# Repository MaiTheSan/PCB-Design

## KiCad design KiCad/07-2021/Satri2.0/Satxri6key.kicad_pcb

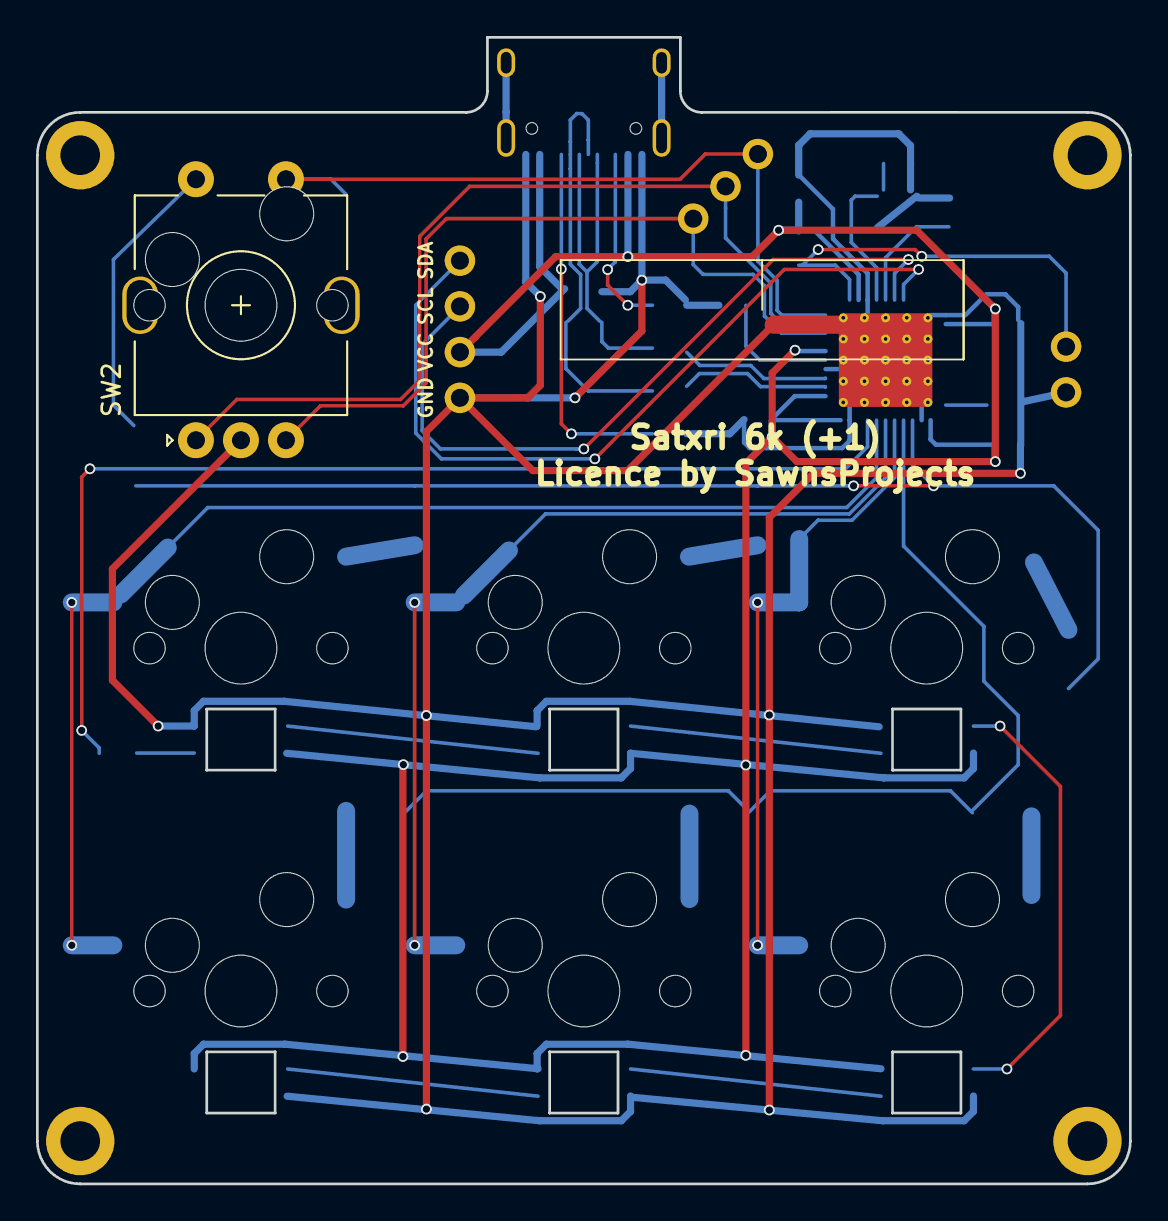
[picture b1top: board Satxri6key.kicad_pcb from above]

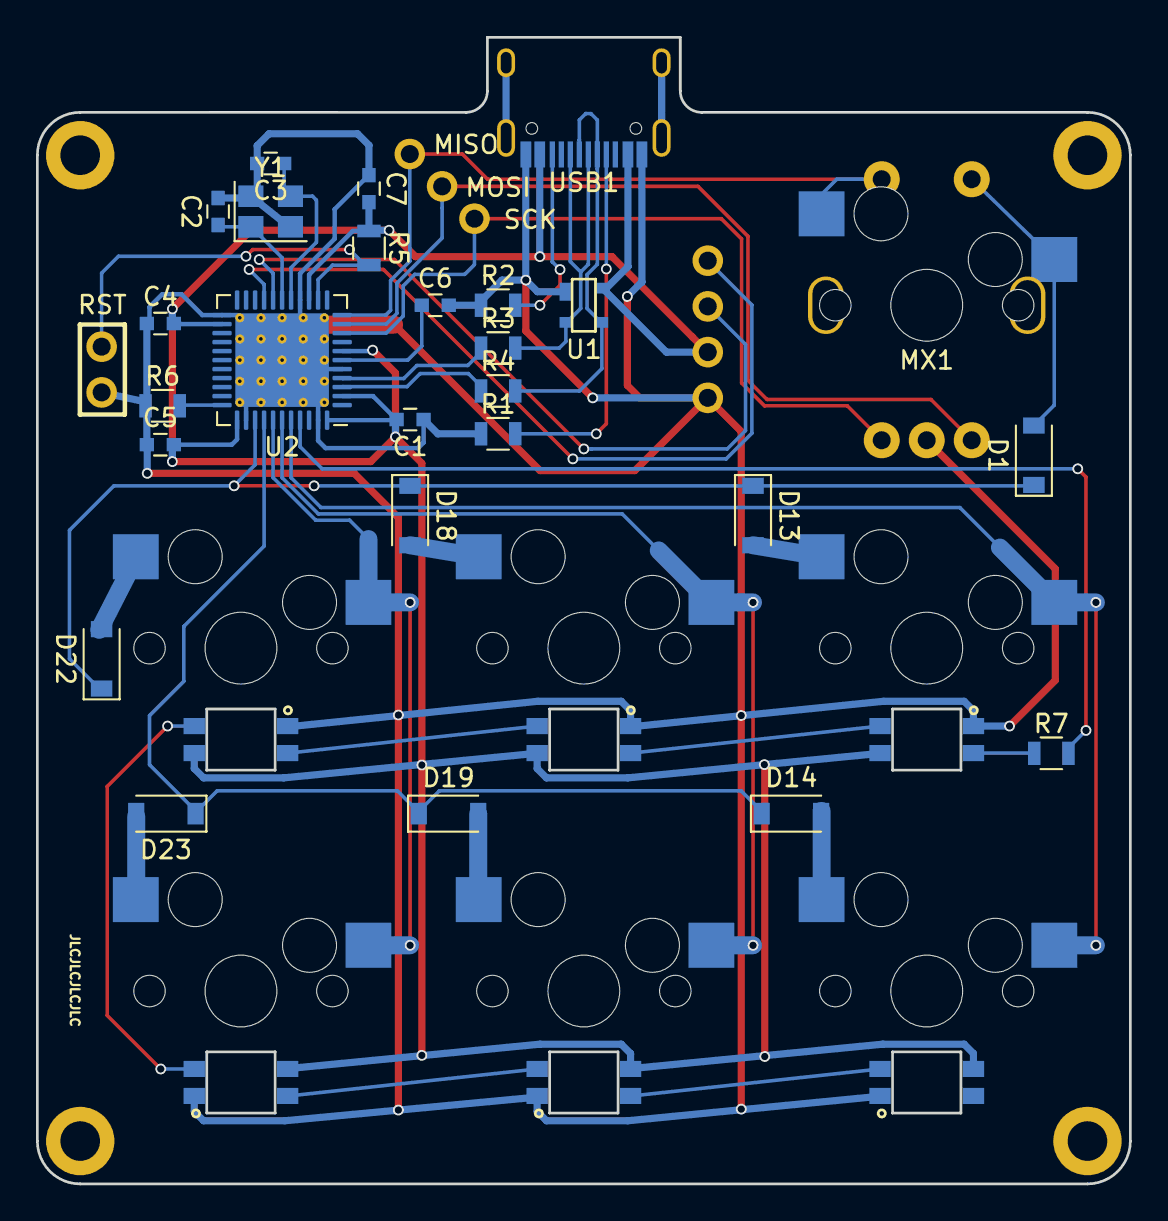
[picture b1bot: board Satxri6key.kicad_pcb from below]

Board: 2 copper layers, 60.7 x 63.7 mm, 46 parts (33 on the bottom side), 37 nets.

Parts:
C1: 10uF; C_0603
C2, C3: 22pF; C_0603
C4, C5, C7: 0.1uF; C_0603
C6: 1uF; C_0603
D1, D13, D14, D18, D19, D22, D23: D; D_SOD-123
LOGO2, LOGO3, LOGO4, LOGO5: Logo_Open_Hardware_Large; MountingHole_2.2mm_M2_DIN965_Pad
MX1, MX15, MX16, MX20, MX21, MX24, MX25: MX-NoLED; MXOnly-1U-Hotswap
R1, R2: 5.1k; R_0805
R3, R4: 22; R_0805
R5: 10k; R_0805
R6: 1k; R_0805
R7: R; R_0805
SK6812MiniE1, SK6812MiniE2, SK6812MiniE3: WS2812B; RGB-6028_FLIPPED
SK6812MiniE4, SK6812MiniE5, SK6812MiniE6: WS2812B; RGB-6028
SW2: Rotary_Encoder_Switch; RotaryEncoder_Alps_EC11E-Switch_Vertical_H20mm_Center
U1: PRTR5V0U2X; SOT143B
U2: ATmega32U4-MU; QFN-44-1EP_7x7mm_P0.5mm_EP5.2x5.2mm_ThermalVias
U3: STF202-22T1G; SSD091
U4, U5: STF202-22T1G; Reset_Pretty
USB1: HRO-TYPE-C-31-M-12; HRO-TYPE-C-31-M-12-Assembly
Y1: 16Mhz; Crystal_SMD_3225-4Pin_3.2x2.5mm

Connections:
+5V: C1.2, C4.2, C5.2, C7.2, R5.1, SK6812MiniE1.1, SK6812MiniE2.1, SK6812MiniE3.1, SK6812MiniE4.1, SK6812MiniE5.1, SK6812MiniE6.1, U1.4, U2.2, U2.7, U2.14, U2.24, U2.34, U2.44, U3.3, USB1.2, USB1.11
COL0: MX15.1, MX16.1, U2.40
COL1: MX20.1, MX21.1, U2.39
COL2: MX24.1, MX25.1, U2.38
D+: R3.1, U2.4
D-: R4.1, U2.3
GND: C1.1, C2.2, C3.2, C4.1, C5.1, C6.2, C7.1, R1.1, R2.1, R6.1, SK6812MiniE1.3, SK6812MiniE2.3, SK6812MiniE3.3, SK6812MiniE4.3, SK6812MiniE5.3, SK6812MiniE6.3, SW2.C, U1.1, U2.5, U2.15, U2.23, U2.35, U2.43, U2.45, U3.4, U5.6, USB1.1, USB1.12, USB1.13, Y1.2, Y1.4
MISO: MX1.2, SW2.S1, U2.11, U4.1
MOSI: SW2.A, U2.10, U4.3
unnamed: C2.1, U2.17, Y1.1
unnamed: C3.1, U2.16, Y1.3
unnamed: C6.1, U2.6
unnamed: D13.2, MX15.2
unnamed: D14.2, MX16.2
unnamed: D18.2, MX20.2
unnamed: D19.2, MX21.2
unnamed: D22.2, MX24.2
unnamed: D23.2, MX25.2
unnamed: R1.2, USB1.4
unnamed: R2.2, USB1.10
unnamed: R3.2, U1.2, USB1.6, USB1.8
unnamed: R4.2, U1.3, USB1.5, USB1.7
unnamed: R6.2, U2.33
unnamed: R7.2, U2.41
unnamed: SK6812MiniE1.2, SK6812MiniE2.4
unnamed: SK6812MiniE2.2, SK6812MiniE3.4
unnamed: SK6812MiniE3.2, SK6812MiniE4.4
unnamed: SK6812MiniE4.2, SK6812MiniE5.4
unnamed: SK6812MiniE5.2, SK6812MiniE6.4
RGBLED: R7.1, SK6812MiniE1.4
ROW0: D1.1, D13.1, D18.1, D22.1, U2.36
ROW1: D14.1, D19.1, D23.1, U2.37
RST: R5.2, U2.13, U5.5
S2: D1.2, MX1.1, SW2.S2
SCK: SW2.B, U2.9, U4.2
SCL: U2.18, U3.2
SDA: U2.19, U3.1

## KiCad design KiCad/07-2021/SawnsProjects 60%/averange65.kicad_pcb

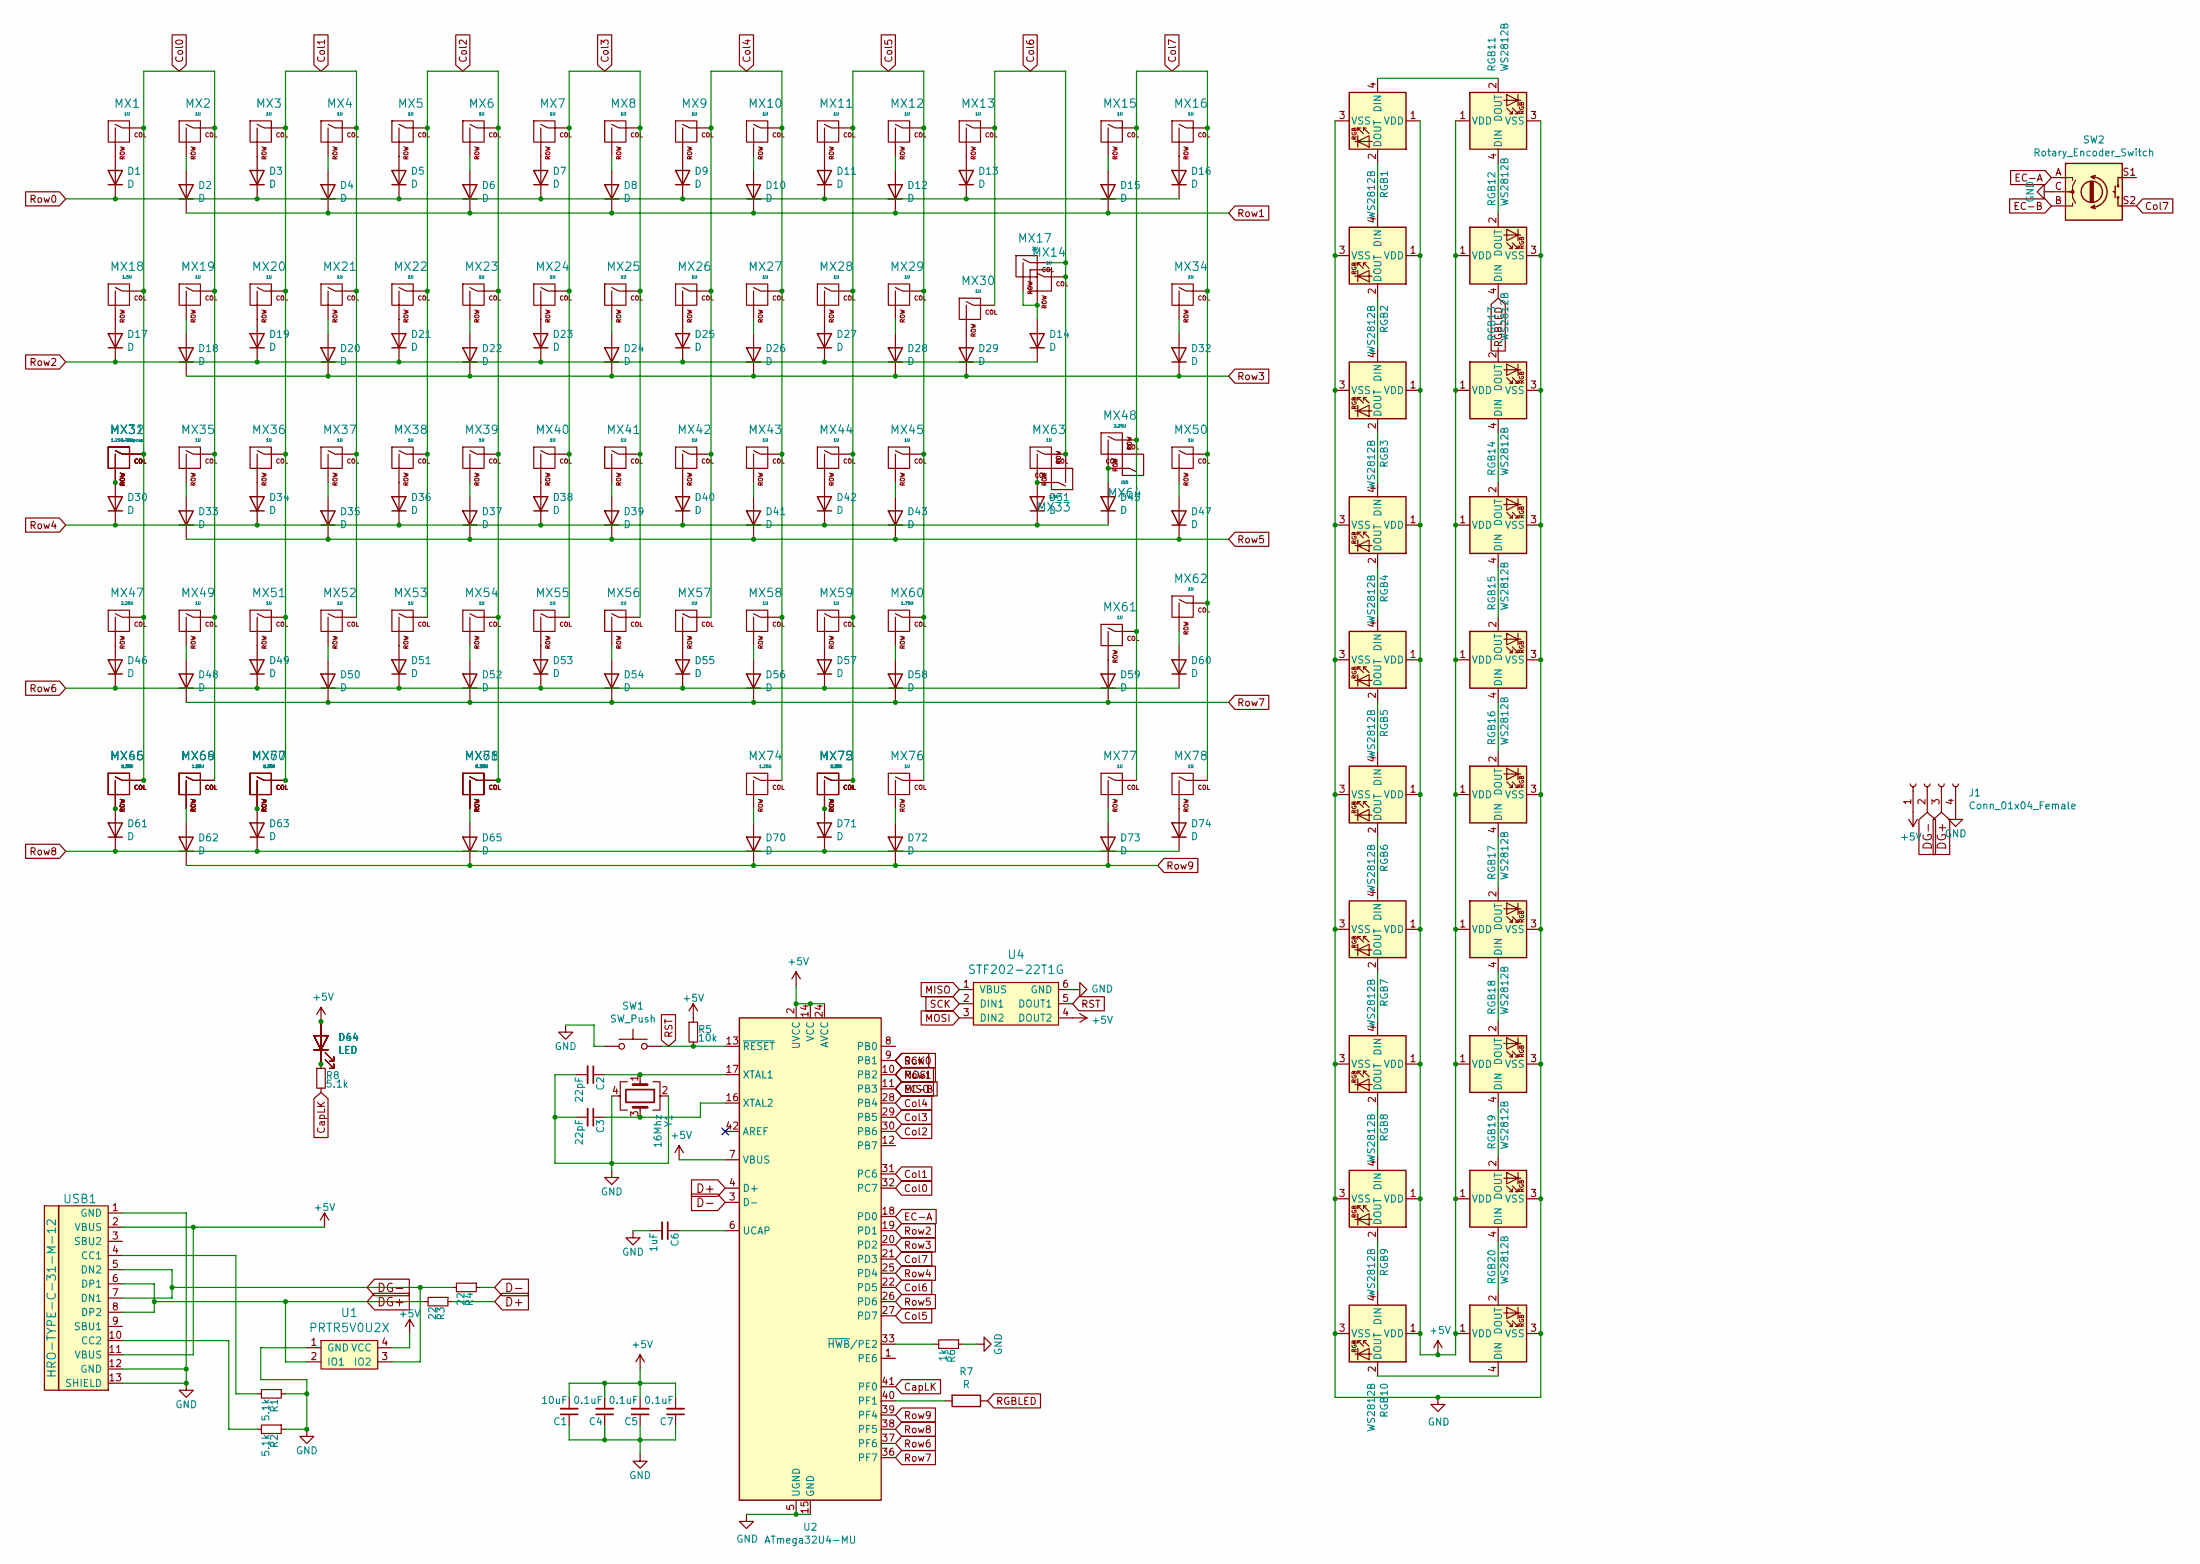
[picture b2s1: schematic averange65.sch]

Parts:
C1: 10uF; C_0603
C2, C3: 22pF; C_0603
C4, C5, C7: 0.1uF; C_0603
C6: 1uF; C_0603
D1, D2, D3, D4, D5, D6, D7, D8, D9, D10, D11, D12, D13, D14, D15, D16, D17, D18, D19, D20, D21, D22, D23, D24, D25, D26, D27, D28, D29, D30, D31, D32, D33, D34, D35, D36, D37, D38, D39, D40, D41, D42, D43, D45, D46, D47, D48, D49, D50, D51, D52, D53, D54, D55, D56, D57, D58, D59, D60, D61, D62, D63, D65, D70, D71, D72, D73, D74: D; D_SOD-123
D44: LED; MXOnly-LEDONLY-FLIPPED
D64: LED; MXOnly-LEDONLY
J1: Conn_01x04_Female; JST-SR-4
MX1, MX2, MX3, MX4, MX5, MX6, MX7, MX8, MX9, MX10, MX11, MX12, MX13, MX14, MX15, MX16, MX19, MX20, MX21, MX22, MX23, MX24, MX25, MX26, MX27, MX28, MX29, MX30, MX34, MX35, MX36, MX37, MX38, MX39, MX40, MX41, MX42, MX43, MX44, MX45, MX49, MX50, MX51, MX52, MX53, MX54, MX55, MX56, MX57, MX58, MX59, MX61, MX62, MX63, MX69, MX76, MX77, MX78: 1U; MXOnly-1U-NoLED
MX17: 2U; MXOnly-2U-NoLED
MX18, MX33, MX46, MX70, MX72: 1.5U; MXOnly-1.5U-NoLED
MX31: 1.25U-stepcap; MXOnly-1.25U-NoLED
MX32, MX60: 1.75U; MXOnly-1.75U-NoLED
MX47, MX48: 2.25U; MXOnly-2.25U-NoLED
MX64: ISO; MXOnly-ISO-ROTATED-ReversedStabilizers-NoLED
MX65, MX66, MX67, MX74, MX75: 1.25U; MXOnly-1.25U-NoLED
MX68: 6.25U; MXOnly-6.25U-ReversedStabilizers-NoLED
MX71: 6.25U; MXOnly-7U-ReversedStabilizers-NoLED
R1, R2, R8: 5.1k; R_0805
R3, R4: 22; R_0805
R5: 10k; R_0805
R6: 1k; R_0805
R7: R; R_0805
RGB1, RGB2, RGB3, RGB4, RGB5, RGB6, RGB7, RGB8, RGB9, RGB10, RGB11, RGB12, RGB13, RGB14, RGB15, RGB16, RGB17, RGB18, RGB19, RGB20: WS2812B; LED_WS2812B_PLCC4_5.0x5.0mm_P3.2mm
SW1: SW_Push; SKQG-1155865
SW2: Rotary_Encoder_Switch; RotaryEncoder_Alps_EC11E-Switch_Vertical_H20mm_Center
U1: PRTR5V0U2X; SOT143B
U2: ATmega32U4-MU; QFN-44-1EP_7x7mm_P0.5mm_EP5.15x5.15mm
U4: STF202-22T1G; Reset_Pretty
USB1: HRO-TYPE-C-31-M-12; HRO-TYPE-C-31-M-12-Assembly
Y1: 16Mhz; Crystal_SMD_3225-4Pin_3.2x2.5mm

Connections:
+5V: C1.2, C4.2, C5.2, C7.2, D44.2 (A), D64.2 (A), J1.1, R5.1, RGB1.1 (VDD), RGB2.1 (VDD), RGB3.1 (VDD), RGB4.1 (VDD), RGB5.1 (VDD), RGB6.1 (VDD), RGB7.1 (VDD), RGB8.1 (VDD), RGB9.1 (VDD), RGB10.1 (VDD), RGB11.1 (VDD), RGB12.1 (VDD), RGB13.1 (VDD), RGB14.1 (VDD), RGB15.1 (VDD), RGB16.1 (VDD), RGB17.1 (VDD), RGB18.1 (VDD), RGB19.1 (VDD), RGB20.1 (VDD), U1.4 (VCC), U2.2 (UVCC), U2.7 (VBUS), U2.14 (VCC), U2.24 (AVCC), U2.34 (VCC), U2.44 (AVCC), U4.4 (DOUT2), USB1.2 (VBUS), USB1.11 (VBUS)
CapLK: R8.2, U2.41 (PF0)
Col0: MX1.1 (COL), MX2.1 (COL), MX18.1 (COL), MX19.1 (COL), MX31.1 (COL), MX32.1 (COL), MX35.1 (COL), MX46.1 (COL), MX47.1 (COL), MX49.1 (COL), MX65.1 (COL), MX66.1 (COL), MX69.1 (COL), U2.32 (PC7)
Col1: MX3.1 (COL), MX4.1 (COL), MX20.1 (COL), MX21.1 (COL), MX36.1 (COL), MX37.1 (COL), MX51.1 (COL), MX52.1 (COL), MX67.1 (COL), MX70.1 (COL), U2.31 (PC6)
Col2: MX5.1 (COL), MX6.1 (COL), MX22.1 (COL), MX23.1 (COL), MX38.1 (COL), MX39.1 (COL), MX53.1 (COL), MX54.1 (COL), MX68.1 (COL), MX71.1 (COL), U2.30 (PB6)
Col3: MX7.1 (COL), MX8.1 (COL), MX24.1 (COL), MX25.1 (COL), MX40.1 (COL), MX41.1 (COL), MX55.1 (COL), MX56.1 (COL), U2.29 (PB5)
Col4: MX9.1 (COL), MX10.1 (COL), MX26.1 (COL), MX27.1 (COL), MX42.1 (COL), MX43.1 (COL), MX57.1 (COL), MX58.1 (COL), MX74.1 (COL), U2.28 (PB4)
Col5: MX11.1 (COL), MX12.1 (COL), MX28.1 (COL), MX29.1 (COL), MX44.1 (COL), MX45.1 (COL), MX59.1 (COL), MX60.1 (COL), MX72.1 (COL), MX75.1 (COL), MX76.1 (COL), U2.27 (PD7)
Col6: MX13.1 (COL), MX14.1 (COL), MX17.1 (COL), MX30.1 (COL), MX33.2 (ROW), MX63.1 (COL), U2.22 (PD5)
Col7: MX15.1 (COL), MX16.1 (COL), MX34.1 (COL), MX48.1 (COL), MX50.1 (COL), MX61.1 (COL), MX62.1 (COL), MX64.2 (ROW), MX77.1 (COL), MX78.1 (COL), SW2.S2, U2.21 (PD3)
D+: R3.1, U2.4 (D+)
D-: R4.1, U2.3 (D-)
DG+: J1.3, R3.2, U1.2 (IO1), USB1.6 (DP1), USB1.8 (DP2)
DG-: J1.2, R4.2, U1.3 (IO2), USB1.5 (DN2), USB1.7 (DN1)
EC-A: SW2.A, U2.18 (PD0)
EC-B: SW2.B, U2.11 (PB3), U4.1 (VBUS)
GND: C1.1, C2.2, C3.2, C4.1, C5.1, C6.2, C7.1, J1.4, R1.1, R2.1, R6.1, RGB1.3 (VSS), RGB2.3 (VSS), RGB3.3 (VSS), RGB4.3 (VSS), RGB5.3 (VSS), RGB6.3 (VSS), RGB7.3 (VSS), RGB8.3 (VSS), RGB9.3 (VSS), RGB10.3 (VSS), RGB11.3 (VSS), RGB12.3 (VSS), RGB13.3 (VSS), RGB14.3 (VSS), RGB15.3 (VSS), RGB16.3 (VSS), RGB17.3 (VSS), RGB18.3 (VSS), RGB19.3 (VSS), RGB20.3 (VSS), SW1.1, SW2.C, U1.1 (GND), U2.5 (UGND), U2.15 (GND), U2.23 (GND), U2.35 (GND), U2.43 (GND), U2.45 (GND), U4.6 (GND), USB1.1 (GND), USB1.12 (GND), USB1.13 (SHIELD), Y1.2, Y1.4
MOSI: D2.1 (K), D4.1 (K), D6.1 (K), D8.1 (K), D10.1 (K), D12.1 (K), D15.1 (K), U2.10 (PB2), U4.3 (DIN2)
unnamed: C2.1, U2.17 (XTAL1), Y1.1
unnamed: C3.1, U2.16 (XTAL2), Y1.3
unnamed: C6.1, U2.6 (UCAP)
unnamed: D1.2 (A), MX1.2 (ROW)
unnamed: D2.2 (A), MX2.2 (ROW)
unnamed: D3.2 (A), MX3.2 (ROW)
unnamed: D4.2 (A), MX4.2 (ROW)
unnamed: D5.2 (A), MX5.2 (ROW)
unnamed: D6.2 (A), MX6.2 (ROW)
unnamed: D7.2 (A), MX7.2 (ROW)
unnamed: D8.2 (A), MX8.2 (ROW)
unnamed: D9.2 (A), MX9.2 (ROW)
unnamed: D10.2 (A), MX10.2 (ROW)
unnamed: D11.2 (A), MX11.2 (ROW)
unnamed: D12.2 (A), MX12.2 (ROW)
unnamed: D13.2 (A), MX13.2 (ROW)
unnamed: D14.2 (A), MX14.2 (ROW), MX17.2 (ROW)
unnamed: D15.2 (A), MX15.2 (ROW)
unnamed: D16.2 (A), MX16.2 (ROW)
unnamed: D17.2 (A), MX18.2 (ROW)
unnamed: D18.2 (A), MX19.2 (ROW)
unnamed: D19.2 (A), MX20.2 (ROW)
unnamed: D20.2 (A), MX21.2 (ROW)
unnamed: D21.2 (A), MX22.2 (ROW)
unnamed: D22.2 (A), MX23.2 (ROW)
unnamed: D23.2 (A), MX24.2 (ROW)
unnamed: D24.2 (A), MX25.2 (ROW)
unnamed: D25.2 (A), MX26.2 (ROW)
unnamed: D26.2 (A), MX27.2 (ROW)
unnamed: D27.2 (A), MX28.2 (ROW)
unnamed: D28.2 (A), MX29.2 (ROW)
unnamed: D29.2 (A), MX30.2 (ROW)
unnamed: D30.2 (A), MX31.2 (ROW), MX32.2 (ROW)
unnamed: D31.2 (A), MX33.1 (COL), MX63.2 (ROW)
unnamed: D32.2 (A), MX34.2 (ROW)
unnamed: D33.2 (A), MX35.2 (ROW)
unnamed: D34.2 (A), MX36.2 (ROW)
unnamed: D35.2 (A), MX37.2 (ROW)
unnamed: D36.2 (A), MX38.2 (ROW)
unnamed: D37.2 (A), MX39.2 (ROW)
unnamed: D38.2 (A), MX40.2 (ROW)
unnamed: D39.2 (A), MX41.2 (ROW)
unnamed: D40.2 (A), MX42.2 (ROW)
unnamed: D41.2 (A), MX43.2 (ROW)
unnamed: D42.2 (A), MX44.2 (ROW)
unnamed: D43.2 (A), MX45.2 (ROW)
unnamed: D44.1 (K), D64.1 (K), R8.1
unnamed: D45.2 (A), MX48.2 (ROW), MX64.1 (COL)
unnamed: D46.2 (A), MX47.2 (ROW)
unnamed: D47.2 (A), MX50.2 (ROW)
unnamed: D48.2 (A), MX49.2 (ROW)
unnamed: D49.2 (A), MX51.2 (ROW)
unnamed: D50.2 (A), MX52.2 (ROW)
unnamed: D51.2 (A), MX53.2 (ROW)
unnamed: D52.2 (A), MX54.2 (ROW)
unnamed: D53.2 (A), MX55.2 (ROW)
unnamed: D54.2 (A), MX56.2 (ROW)
unnamed: D55.2 (A), MX57.2 (ROW)
unnamed: D56.2 (A), MX58.2 (ROW)
unnamed: D57.2 (A), MX59.2 (ROW)
unnamed: D58.2 (A), MX60.2 (ROW)
unnamed: D59.2 (A), MX61.2 (ROW)
unnamed: D60.2 (A), MX62.2 (ROW)
unnamed: D61.2 (A), MX46.2 (ROW), MX65.2 (ROW)
unnamed: D62.2 (A), MX66.2 (ROW), MX69.2 (ROW)
unnamed: D63.2 (A), MX67.2 (ROW), MX70.2 (ROW)
unnamed: D65.2 (A), MX68.2 (ROW), MX71.2 (ROW)
unnamed: D70.2 (A), MX74.2 (ROW)
unnamed: D71.2 (A), MX72.2 (ROW), MX75.2 (ROW)
unnamed: D72.2 (A), MX76.2 (ROW)
unnamed: D73.2 (A), MX77.2 (ROW)
unnamed: D74.2 (A), MX78.2 (ROW)
unnamed: R1.2, USB1.4 (CC1)
unnamed: R2.2, USB1.10 (CC2)
unnamed: R6.2, U2.33 (~HWB~/PE2)
unnamed: R7.2, U2.40 (PF1)
unnamed: RGB1.2 (DOUT), RGB2.4 (DIN)
unnamed: RGB1.4 (DIN), RGB11.2 (DOUT)
unnamed: RGB2.2 (DOUT), RGB3.4 (DIN)
unnamed: RGB3.2 (DOUT), RGB4.4 (DIN)
unnamed: RGB4.2 (DOUT), RGB5.4 (DIN)
unnamed: RGB5.2 (DOUT), RGB6.4 (DIN)
unnamed: RGB6.2 (DOUT), RGB7.4 (DIN)
unnamed: RGB7.2 (DOUT), RGB8.4 (DIN)
unnamed: RGB8.2 (DOUT), RGB9.4 (DIN)
unnamed: RGB10.2 (DOUT), RGB20.4 (DIN)
unnamed: RGB9.2 (DOUT), RGB10.4 (DIN)
unnamed: RGB11.4 (DIN), RGB12.2 (DOUT)
unnamed: RGB13.4 (DIN), RGB14.2 (DOUT)
unnamed: RGB14.4 (DIN), RGB15.2 (DOUT)
unnamed: RGB15.4 (DIN), RGB16.2 (DOUT)
unnamed: RGB16.4 (DIN), RGB17.2 (DOUT)
unnamed: RGB17.4 (DIN), RGB18.2 (DOUT)
unnamed: RGB18.4 (DIN), RGB19.2 (DOUT)
unnamed: RGB19.4 (DIN), RGB20.2 (DOUT)
RGBLED: R7.1, RGB12.4 (DIN)
RST: R5.2, SW1.2, U2.13 (~RESET), U4.5 (DOUT1)
Row0: D1.1 (K), D3.1 (K), D5.1 (K), D7.1 (K), D9.1 (K), D11.1 (K), D13.1 (K), D16.1 (K), U2.9 (PB1), U4.2 (DIN1)
Row2: D14.1 (K), D17.1 (K), D19.1 (K), D21.1 (K), D23.1 (K), D25.1 (K), D27.1 (K), U2.19 (PD1)
Row3: D18.1 (K), D20.1 (K), D22.1 (K), D24.1 (K), D26.1 (K), D28.1 (K), D29.1 (K), D32.1 (K), U2.20 (PD2)
Row4: D30.1 (K), D31.1 (K), D34.1 (K), D36.1 (K), D38.1 (K), D40.1 (K), D42.1 (K), D45.1 (K), U2.25 (PD4)
Row5: D33.1 (K), D35.1 (K), D37.1 (K), D39.1 (K), D41.1 (K), D43.1 (K), D47.1 (K), U2.26 (PD6)
Row6: D46.1 (K), D49.1 (K), D51.1 (K), D53.1 (K), D55.1 (K), D57.1 (K), D60.1 (K), U2.37 (PF6)
Row7: D48.1 (K), D50.1 (K), D52.1 (K), D54.1 (K), D56.1 (K), D58.1 (K), D59.1 (K), U2.36 (PF7)
Row8: D61.1 (K), D63.1 (K), D71.1 (K), D74.1 (K), U2.38 (PF5)
Row9: D62.1 (K), D65.1 (K), D70.1 (K), D72.1 (K), D73.1 (K), U2.39 (PF4)

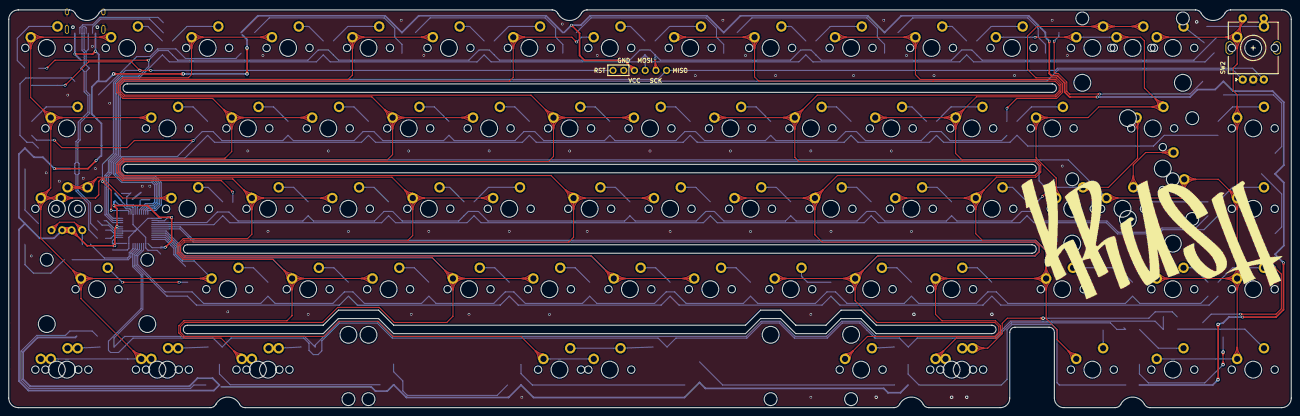
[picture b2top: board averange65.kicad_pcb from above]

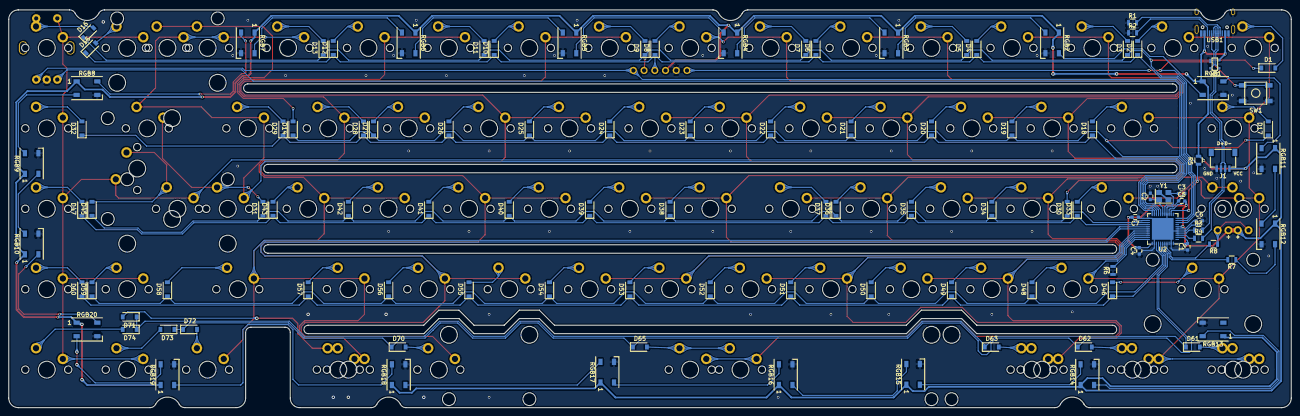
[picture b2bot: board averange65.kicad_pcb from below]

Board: 2 copper layers, 303.8 x 94.2 mm, 190 parts (109 on the bottom side), 124 nets.

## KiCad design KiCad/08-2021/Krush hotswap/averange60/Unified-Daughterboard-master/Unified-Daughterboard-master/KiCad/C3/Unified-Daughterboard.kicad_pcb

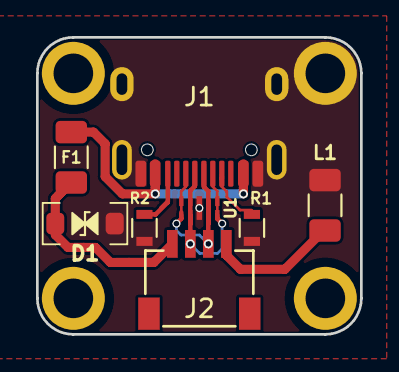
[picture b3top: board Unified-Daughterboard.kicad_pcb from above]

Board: 2 copper layers, 18.0 x 16.5 mm, 12 parts (0 on the bottom side), 8 nets.

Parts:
D1: SMF9.0CA; D_SOD-123_Bidirectional
F1: ASMD1206-150; Fuse_1206_3216Metric
J1: TYPE-C-31-M12_13; TYPE-C-31-M-12
J2: SM04B-SRSS-TB(LF)(SN); JST-SR-4
L1: 60R@100MHz; L_1206_3216Metric
MH1, MH2, MH3, MH4: Mount-M2; Generic-Mounthole
R1, R2: 5.1k; R_0603
U1: TPD4E05U06DQAR; USON-10_2.5x1.0mm_P0.5mm

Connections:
DA+: J1.A6, J1.B6, J2.3, U1.1, U1.4, U1.7, U1.10
DA-: J1.A7, J1.B7, J2.2, U1.2, U1.5, U1.6, U1.9
GND: J2.4, L1.1
GNDPWR: D1.1, J1.A1, J1.B1, J1.S, L1.2, MH2.1, R1.2, R2.2, U1.3, U1.8
unnamed: J1.A5, R1.1
unnamed: J1.B5, R2.1
VBUS: F1.1, J1.A4, J1.B4
VCC: D1.2, F1.2, J2.1
